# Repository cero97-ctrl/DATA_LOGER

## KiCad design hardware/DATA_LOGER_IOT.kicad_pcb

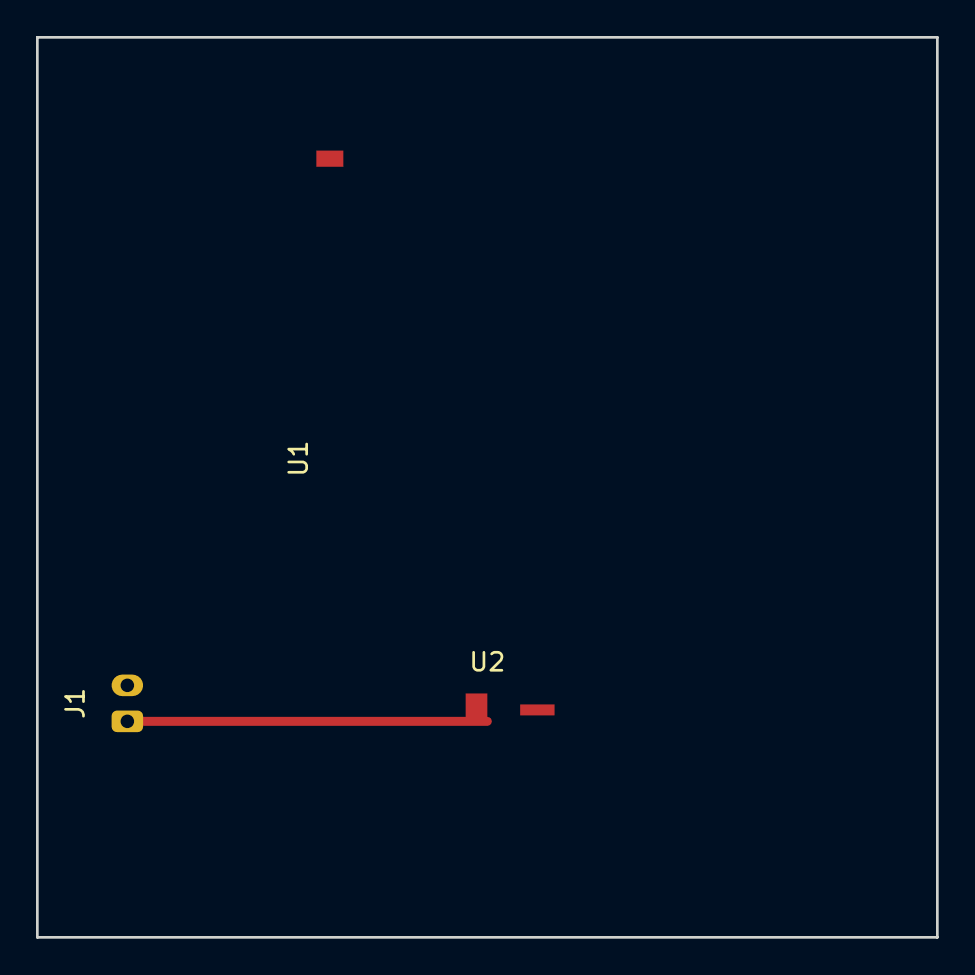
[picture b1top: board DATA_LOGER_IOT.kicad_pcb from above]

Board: 2 copper layers, 50.0 x 50.0 mm, 3 parts (0 on the bottom side), 2 nets.

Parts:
J1: JST_PH_B2B-PH-K_1x02_P2.00mm_Vertical
U1: ESP32-S3; ESP32-S3-WROOM-1
U2: TI_SO-PowerPAD-8

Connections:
+12V: J1.1, U2.7
GND: J1.2, U1.1, U2.9

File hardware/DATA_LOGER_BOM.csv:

Item,Quantity,Reference(s),Value,Footprint
1,1,U1,ESP32-S3-WROOM-1,ESP32-S3-WROOM-1
2,1,J1,JST_PH_B2B-PH-K,Connector_JST:JST_PH_B2B-PH-K_1x02_P2.00mm_Vertical
3,1,U2,TI_SO-PowerPAD-8,Package_SO:TI_SO-PowerPAD-8

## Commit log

2026-04-11 Initial commit for DATA_LOGER
2026-04-12 WIP: guardar cambios antes de pull
